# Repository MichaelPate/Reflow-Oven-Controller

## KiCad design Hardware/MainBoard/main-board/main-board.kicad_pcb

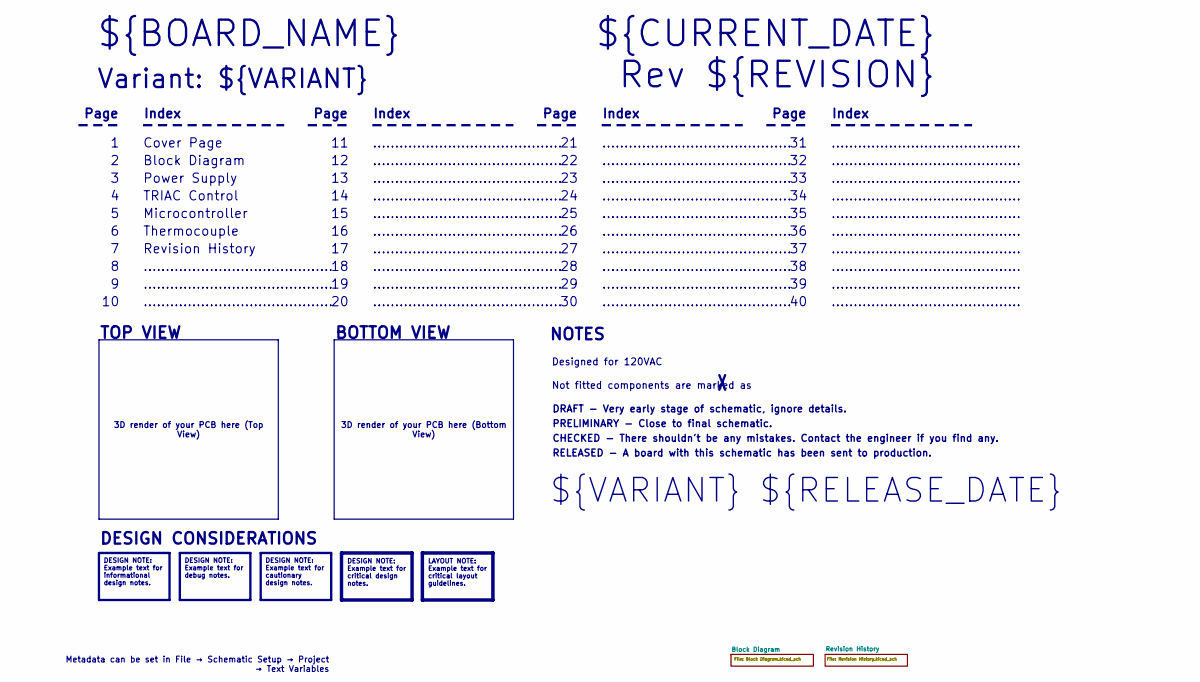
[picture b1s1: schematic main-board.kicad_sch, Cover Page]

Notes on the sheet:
BOTTOM VIEW
...........................................
RELEASED - A board with this schematic has been sent to production.
Page
TOP VIEW
Not fitted components are marked as
Index
PRELIMINARY - Close to final schematic.
${VARIANT} ${RELEASE_DATE}
TRIAC Control
${CURRENT_DATE}
Variant: ${VARIANT}
Rev ${REVISION}
Microcontroller
${BOARD_NAME}
DRAFT - Very early stage of schematic, ignore details.
Thermocouple
Block Diagram
Designed for 120VAC
Cover Page
NOTES
Power Supply
CHECKED - There shouldn't be any mistakes. Contact the engineer if you find any.
DESIGN CONSIDERATIONS
Revision History
3D render of your PCB here (Bottom View)
3D render of your PCB here (Top View)
Metadata can be set in File → Schematic Setup → Project → Text Variables
DESIGN NOTE: Example text for informational design notes.
LAYOUT NOTE: Example text for critical layout guidelines.
DESIGN NOTE: Example text for cautionary design notes.
DESIGN NOTE: Example text for debug notes.
DESIGN NOTE: Example text for critical design notes.

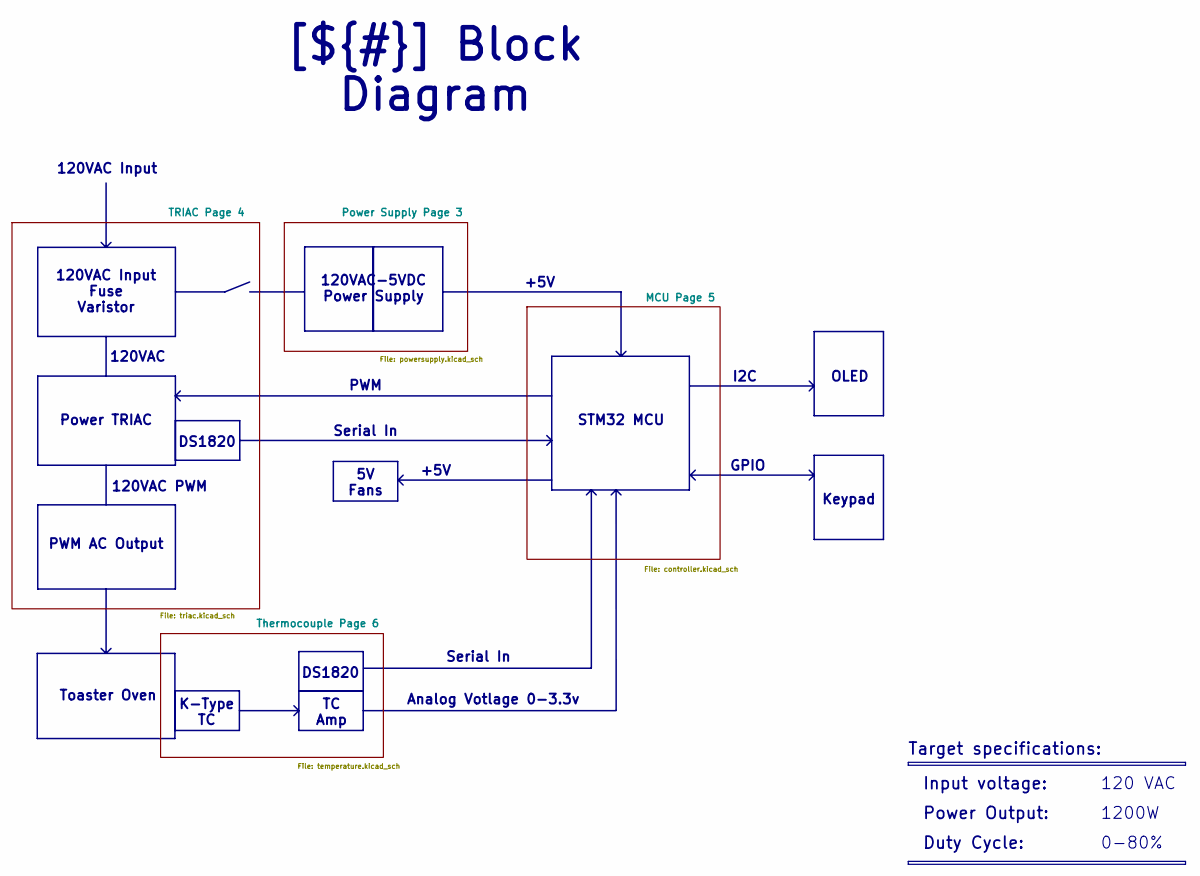
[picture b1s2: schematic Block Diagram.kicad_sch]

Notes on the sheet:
TC Amp
DS1820
PWM AC Output
+5V
GPIO
Toaster Oven
STM32 MCU
PWM
K-Type TC
120VAC
Analog Votlage 0-3.3v
5V Fans
120VAC Input
OLED
Power TRIAC
Serial In
120VAC-5VDC Power Supply
120VAC Input Fuse Varistor
120VAC PWM
Keypad
I2C
Duty Cycle:
Power Output:
Input voltage:
1200W
[${#}] ${TITLE}
Target specifications:
0-80%
120 VAC

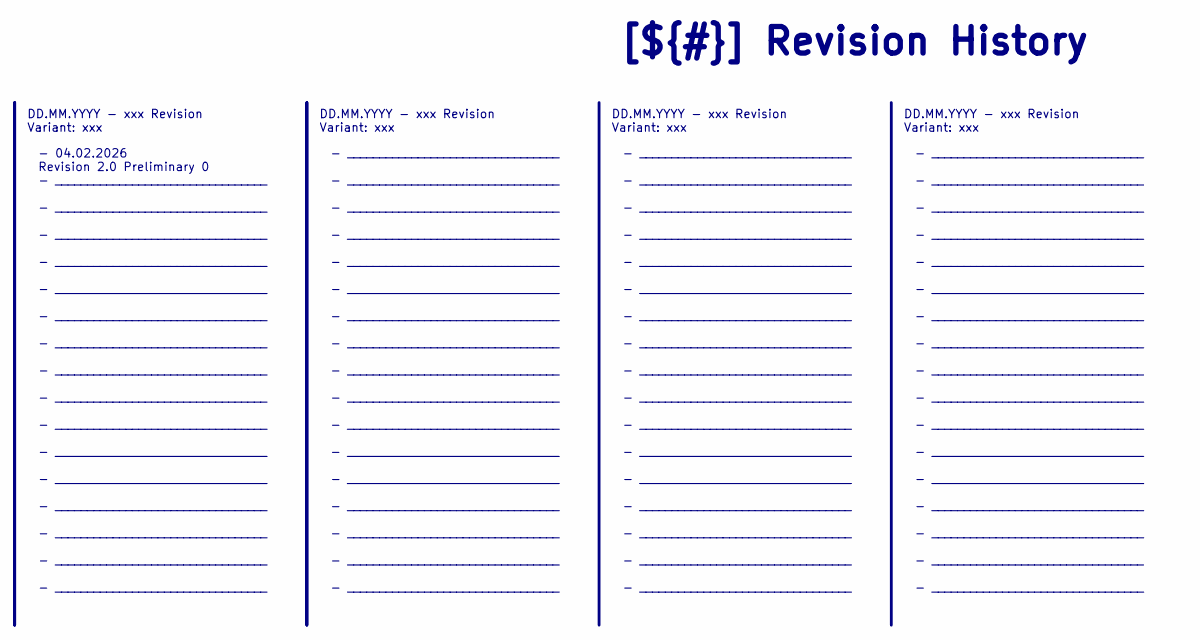
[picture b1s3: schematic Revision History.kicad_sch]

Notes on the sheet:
DD.MM.YYYY - xxx Revision Variant: xxx
[${#}] ${TITLE}
- _________________________________ - _________________________________ - _________________________________ - _________________________________ - _________________________________ - _________________________________ - _________________________________ - _________________________________ - _________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
- 04.02.2026 Revision 2.0 Preliminary 0 - _________________________________ - _________________________________ - _________________________________ - _________________________________ - _________________________________ - _________________________________ - _________________________________ - _____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

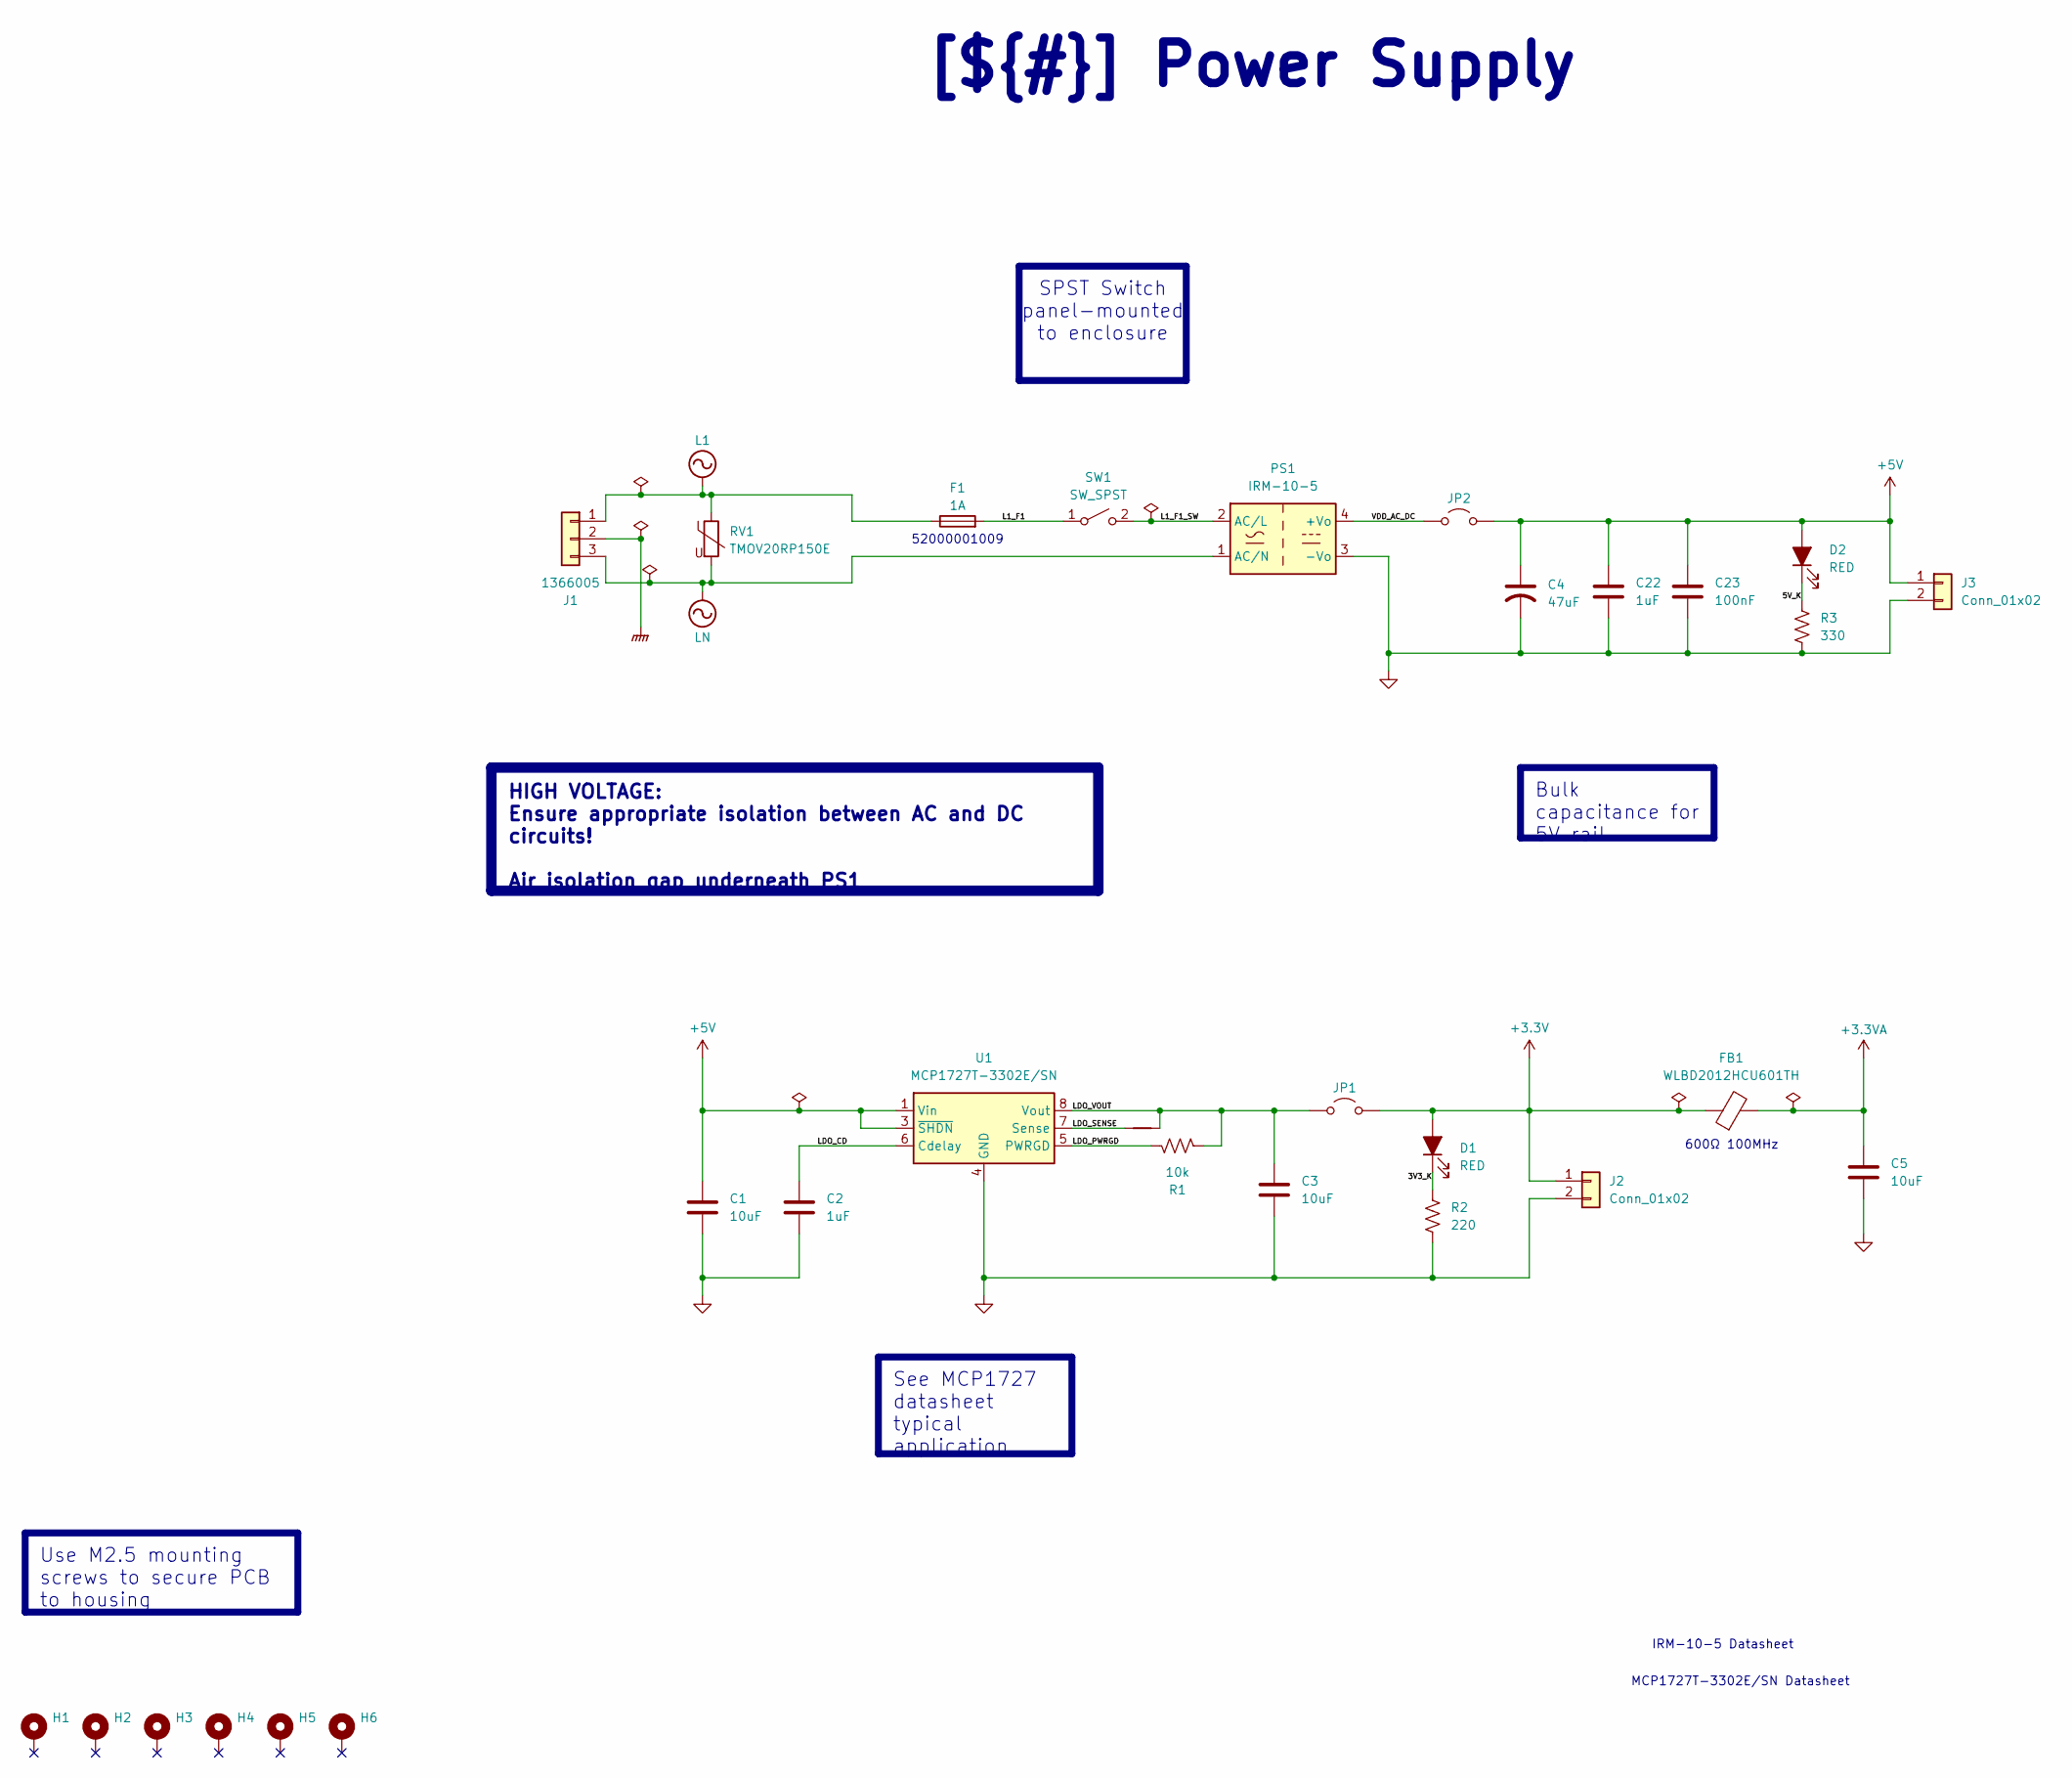
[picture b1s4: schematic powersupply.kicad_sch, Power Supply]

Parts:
C1, C3, C5: 10uF; C_0805_2012Metric_Pad1.18x1.45mm_HandSolder
C2, C22: 1uF; C_0805_2012Metric_Pad1.18x1.45mm_HandSolder
C4: 47uF; C_Radial_D5.0mm_H5.0mm_P2.00mm
C23: 100nF; C_0603_1608Metric_Pad1.08x0.95mm_HandSolder
D1, D2: RED; LED_0603_1608Metric_Pad1.05x0.95mm_HandSolder
F1: 1A; Fuseholder_Clip-5x20mm_Littelfuse_100_Inline_P20.50x4.60mm_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
FB1: WLBD2012HCU601TH; L_0805_2012Metric_Pad1.05x1.20mm_HandSolder
H1, H2, H3, H4, H5, H6: MountingHole_Pad; MountingHole_2.7mm
J1: 1366005; SPTA-THR 2.53-5.0 P26
J2, J3: Conn_01x02; TerminalBlock_Phoenix_MKDS-1,5-2-5.08_1x02_P5.08mm_Horizont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
JP1, JP2: Jumper_2_Open; PinHeader_1x02_P2.54mm_Vertical
NT2: NetTie_2; NetTie-2_SMD_Pad0.5mm
PS1: IRM-10-5; Converter_ACDC_MeanWell_IRM-10-xx_THT
R1: 10k; R_0603_1608Metric_Pad0.98x0.95mm_HandSolder
R2: 220; R_0603_1608Metric_Pad0.98x0.95mm_HandSolder
R3: 330; R_0603_1608Metric_Pad0.98x0.95mm_HandSolder
RV1: TMOV20RP150E
SW1: SW_SPST; TerminalBlock_Phoenix_MKDS-1,5-2-5.08_1x02_P5.08mm_Horizont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
U1: MCP1727T-3302E/SN; SOIC-8_3.9x4.9mm_P1.27mm

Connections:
+3.3V: D1.2 (A), FB1.1, J2.1, JP1.2 (B); also elsewhere on the board
+3.3VA: C5.1, FB1.2; also elsewhere on the board
+5V: C1.1, C4.1, C22.1, C23.1, D2.2 (A), J3.1, JP2.2 (B), U1.1 (Vin), U1.2 (Vin), U1.3 (~SHDN); also elsewhere on the board
/Block Diagram/Power Supply Page 3/3V3_K: D1.1 (K), R2.1
/Block Diagram/Power Supply Page 3/5V_K: D2.1 (K), R3.1
/Block Diagram/Power Supply Page 3/L1_F1: F1.2, SW1.1 (A)
/Block Diagram/Power Supply Page 3/L1_F1_SW: PS1.2 (AC/L), SW1.2 (B)
/Block Diagram/Power Supply Page 3/LDO_CD: C2.1, U1.6 (Cdelay)
/Block Diagram/Power Supply Page 3/LDO_PWRGD: R1.2, U1.5 (PWRGD)
/Block Diagram/Power Supply Page 3/LDO_SENSE: NT2.1, U1.7 (Sense)
/Block Diagram/Power Supply Page 3/LDO_VOUT: C3.1, JP1.1 (A), NT2.2, R1.1, U1.8 (Vout)
/Block Diagram/Power Supply Page 3/VDD_AC_DC: JP2.1 (A), PS1.4 (+Vo)
GND: C1.2, C2.2, C3.2, C4.2, C5.2, C22.2, C23.2, J2.2, J3.2, PS1.3 (-Vo), R2.2, R3.2, U1.4 (GND); also elsewhere on the board
GNDPWR: J1.2; also elsewhere on the board
L1: F1.1, J1.1, RV1.1; also elsewhere on the board
LN: J1.3, PS1.1 (AC/N), RV1.2; also elsewhere on the board

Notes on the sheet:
52000001009
600Ω 100MHz
IRM-10-5 Datasheet
MCP1727T-3302E/SN Datasheet
See MCP1727 datasheet typical application
Bulk capacitance for 5V rail
Use M2.5 mounting screws to secure PCB to housing
[${#}] ${TITLE}
SPST Switch panel-mounted to enclosure
HIGH VOLTAGE: Ensure appropriate isolation between AC and DC circuits! Air isolation gap underneath PS1

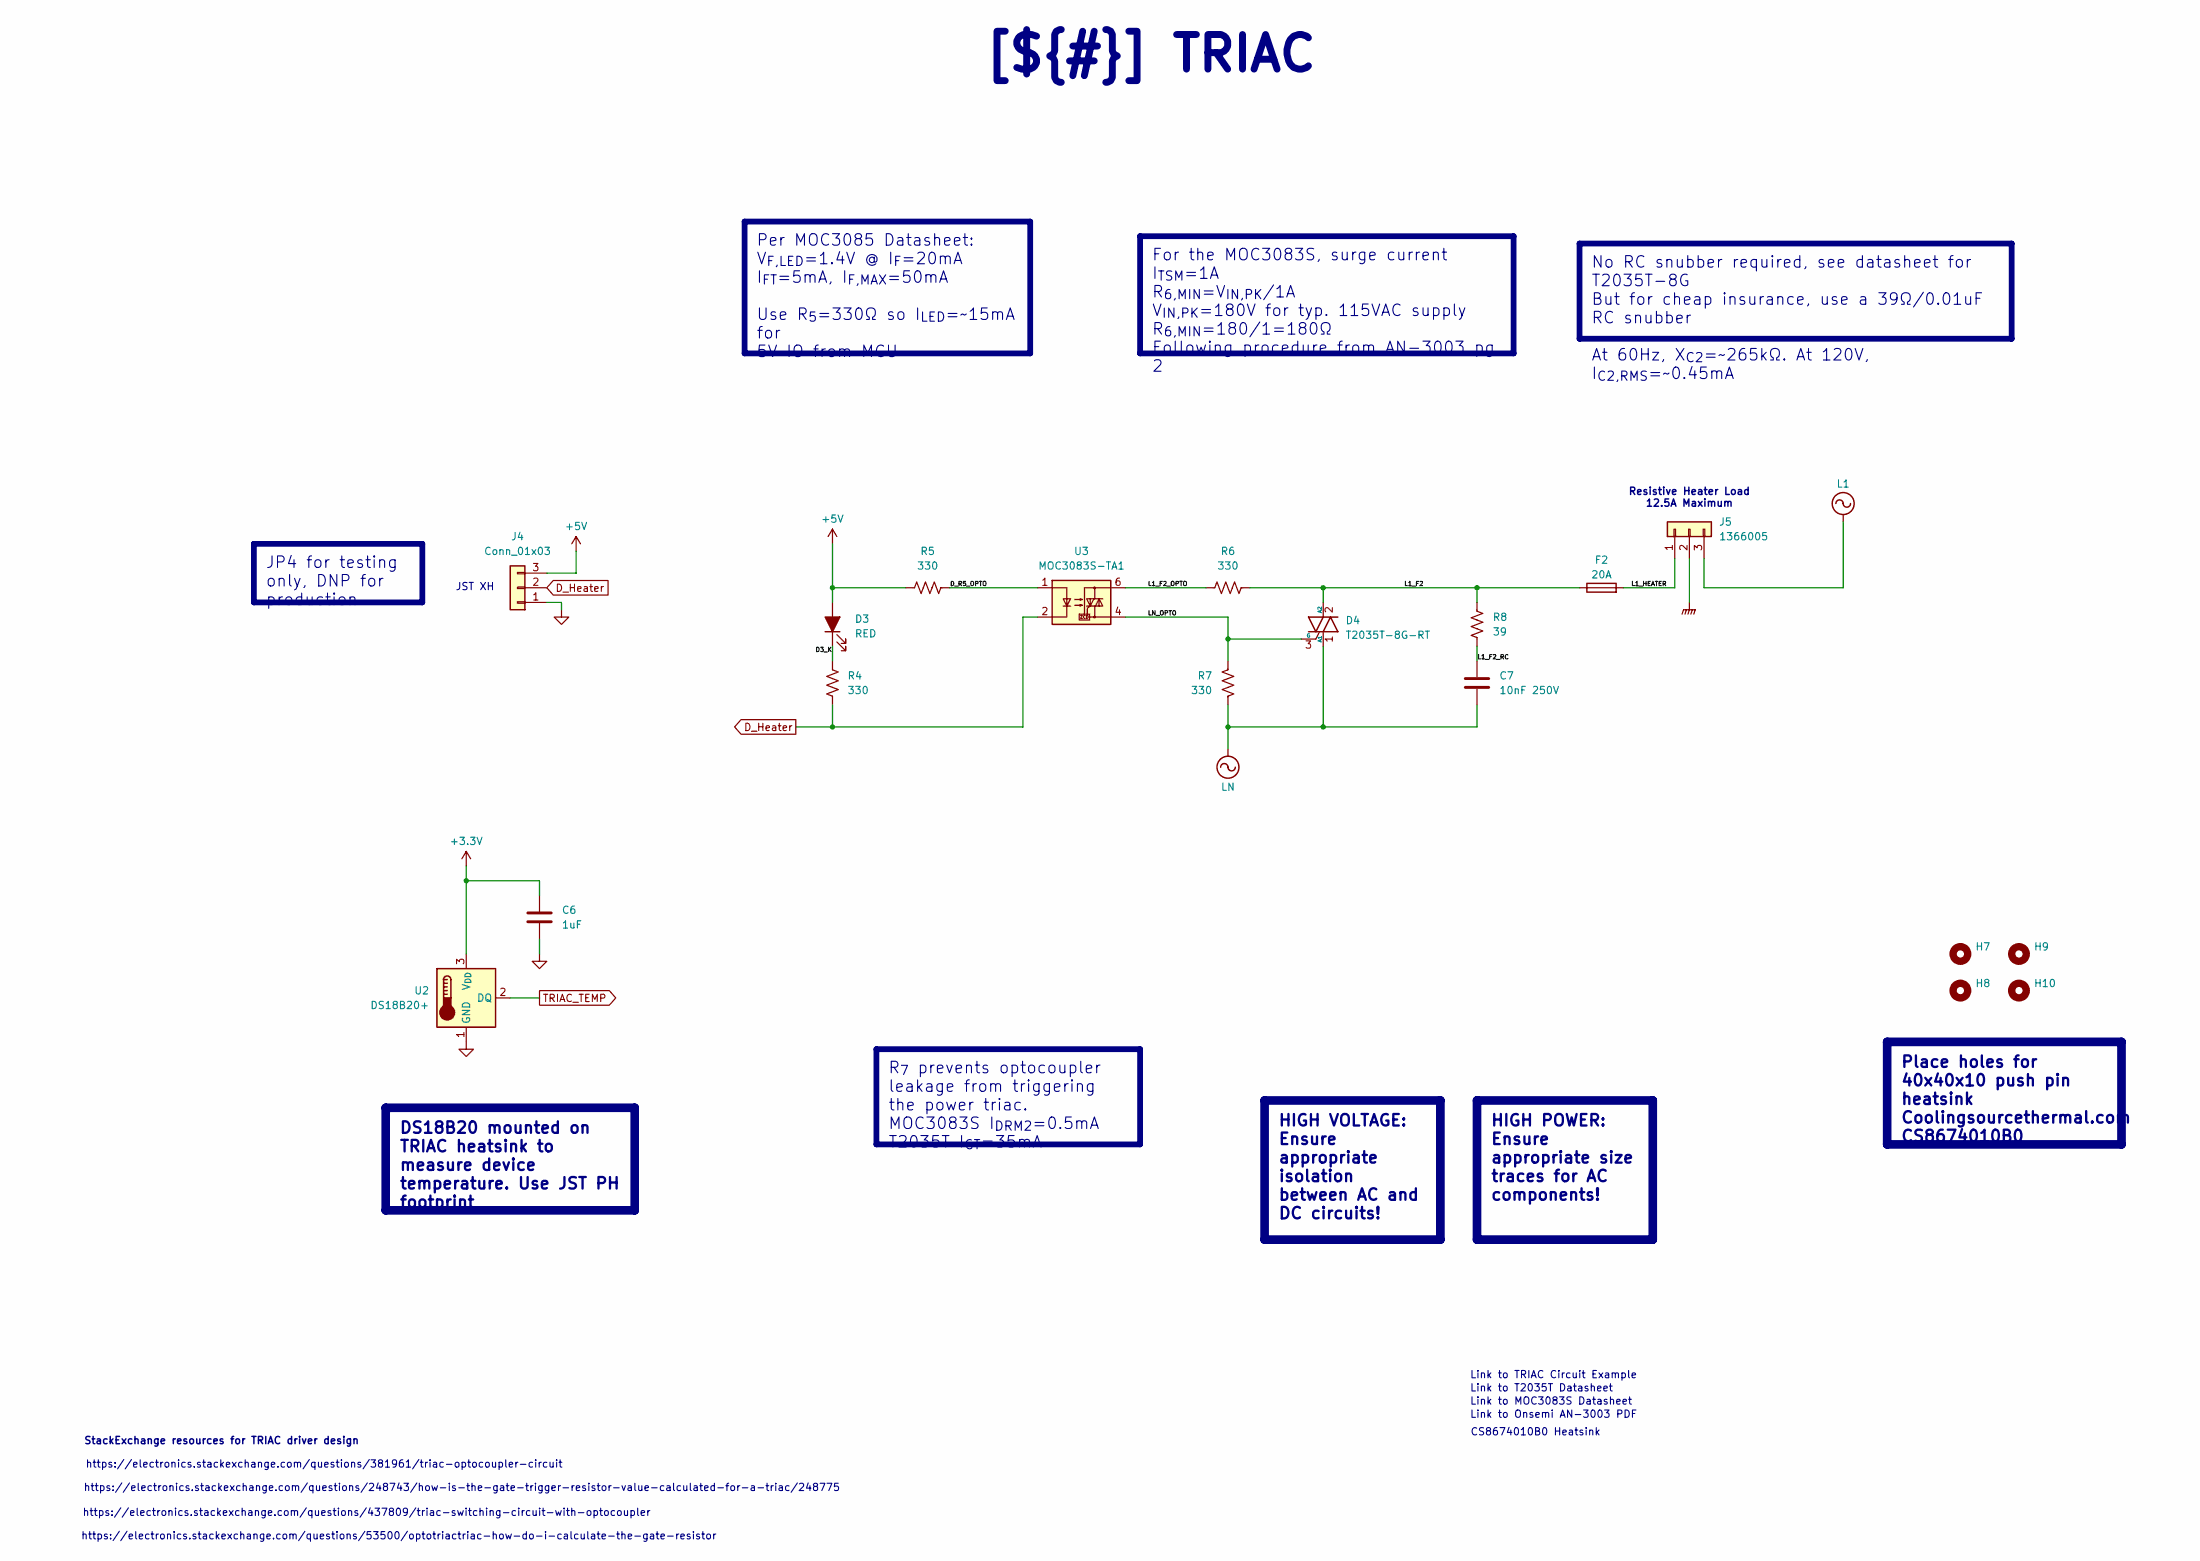
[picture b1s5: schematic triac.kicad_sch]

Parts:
C6: 1uF; C_0805_2012Metric_Pad1.18x1.45mm_HandSolder
C7: 10nF 250V; C_1812_4532Metric_Pad1.57x3.40mm_HandSolder
D3: RED; LED_0603_1608Metric_Pad1.05x0.95mm_HandSolder
D4: T2035T-8G-RT; TO-263-2
F2: 20A; Fuseholder_Clip-6.3x32mm_Littelfuse_122_Inline_P34.21x7.62m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
H7, H8, H9, H10: MountingHole; MountingHole_3mm
J4: Conn_01x03; JST_XH_B3B-XH-A_1x03_P2.50mm_Vertical
J5: 1366005; SPTA-THR 2.53-5.0 P26
R4, R5: 330; R_0603_1608Metric_Pad0.98x0.95mm_HandSolder
R6, R7: 330; R_2512_6332Metric_Pad1.40x3.35mm_HandSolder
R8: 39; R_2512_6332Metric_Pad1.40x3.35mm_HandSolder
U2: DS18B20+; JST_PH_B3B-PH-K_1x03_P2.00mm_Vertical
U3: MOC3083S-TA1; SMDIP-6_W9.53mm

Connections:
+3.3V: C6.1, U2.3 (V_{DD}); also elsewhere on the board
+5V: D3.2 (A), J4.3, R5.1; also elsewhere on the board
/Block Diagram/TRIAC Page 4/D3_K: D3.1 (K), R4.1
/Block Diagram/TRIAC Page 4/D_R5_OPTO: R5.2, U3.1
/Block Diagram/TRIAC Page 4/L1_F2: D4.2 (A2), F2.1, R6.2, R8.2
/Block Diagram/TRIAC Page 4/L1_F2_OPTO: R6.1, U3.6
/Block Diagram/TRIAC Page 4/L1_F2_RC: C7.1, R8.1
/Block Diagram/TRIAC Page 4/L1_HEATER: F2.2, J5.1
/Block Diagram/TRIAC Page 4/LN_OPTO: D4.3 (G), R7.2, U3.4
D_Heater: J4.2, R4.2, U3.2; also elsewhere on the board
GND: C6.2, J4.1, U2.1 (GND); also elsewhere on the board
GNDPWR: J5.2; also elsewhere on the board
L1: J5.3; also elsewhere on the board
LN: C7.2, D4.1 (A1), R7.1; also elsewhere on the board
TRIAC_TEMP: U2.2 (DQ); also elsewhere on the board

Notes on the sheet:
JST XH
Link to Onsemi AN-3003 PDF
https://electronics.stackexchange.com/questions/381961/triac-optocoupler-circuit
https://electronics.stackexchange.com/questions/53500/optotriactriac-how-do-i-calculate-the-gate-resistor
StackExchange resources for TRIAC driver design
Link to TRIAC Circuit Example
https://electronics.stackexchange.com/questions/437809/triac-switching-circuit-with-optocoupler
Link to MOC3083S Datasheet
https://electronics.stackexchange.com/questions/248743/how-is-the-gate-trigger-resistor-value-calculated-for-a-triac/248775
Resistive Heater Load 12.5A Maximum
CS8674010B0 Heatsink
Link to T2035T Datasheet
No RC snubber required, see datasheet for T2035T-8G But for cheap insurance, use a 39Ω/0.01uF RC snubber At 60Hz, X_{C2}=~265kΩ. At 120V, I_{C2,RMS}=~0.45mA
Place holes for 40x40x10 push pin heatsink Coolingsourcethermal.com CS8674010B0
HIGH VOLTAGE: Ensure appropriate isolation between AC and DC circuits!
HIGH POWER: Ensure appropriate size traces for AC components!
[${#}] ${TITLE}
JP4 for testing only, DNP for production
DS18B20 mounted on TRIAC heatsink to measure device temperature. Use JST PH footprint
R_{7} prevents optocoupler leakage from triggering the power triac. MOC3083S I_{DRM2}=0.5mA T2035T I_{GT}=35mA
For the MOC3083S, surge current I_{TSM}=1A R_{6,MIN}=V_{IN,PK}/1A V_{IN,PK}=180V for typ. 115VAC supply R_{6,MIN}=180/1=180Ω Following procedure from AN-3003 pg. 2
Per MOC3085 Datasheet: V_{F,LED}=1.4V @ I_{F}=20mA I_{FT}=5mA, I_{F,MAX}=50mA Use R_{5}=330Ω so I_{LED}=~15mA for 5V IO from MCU

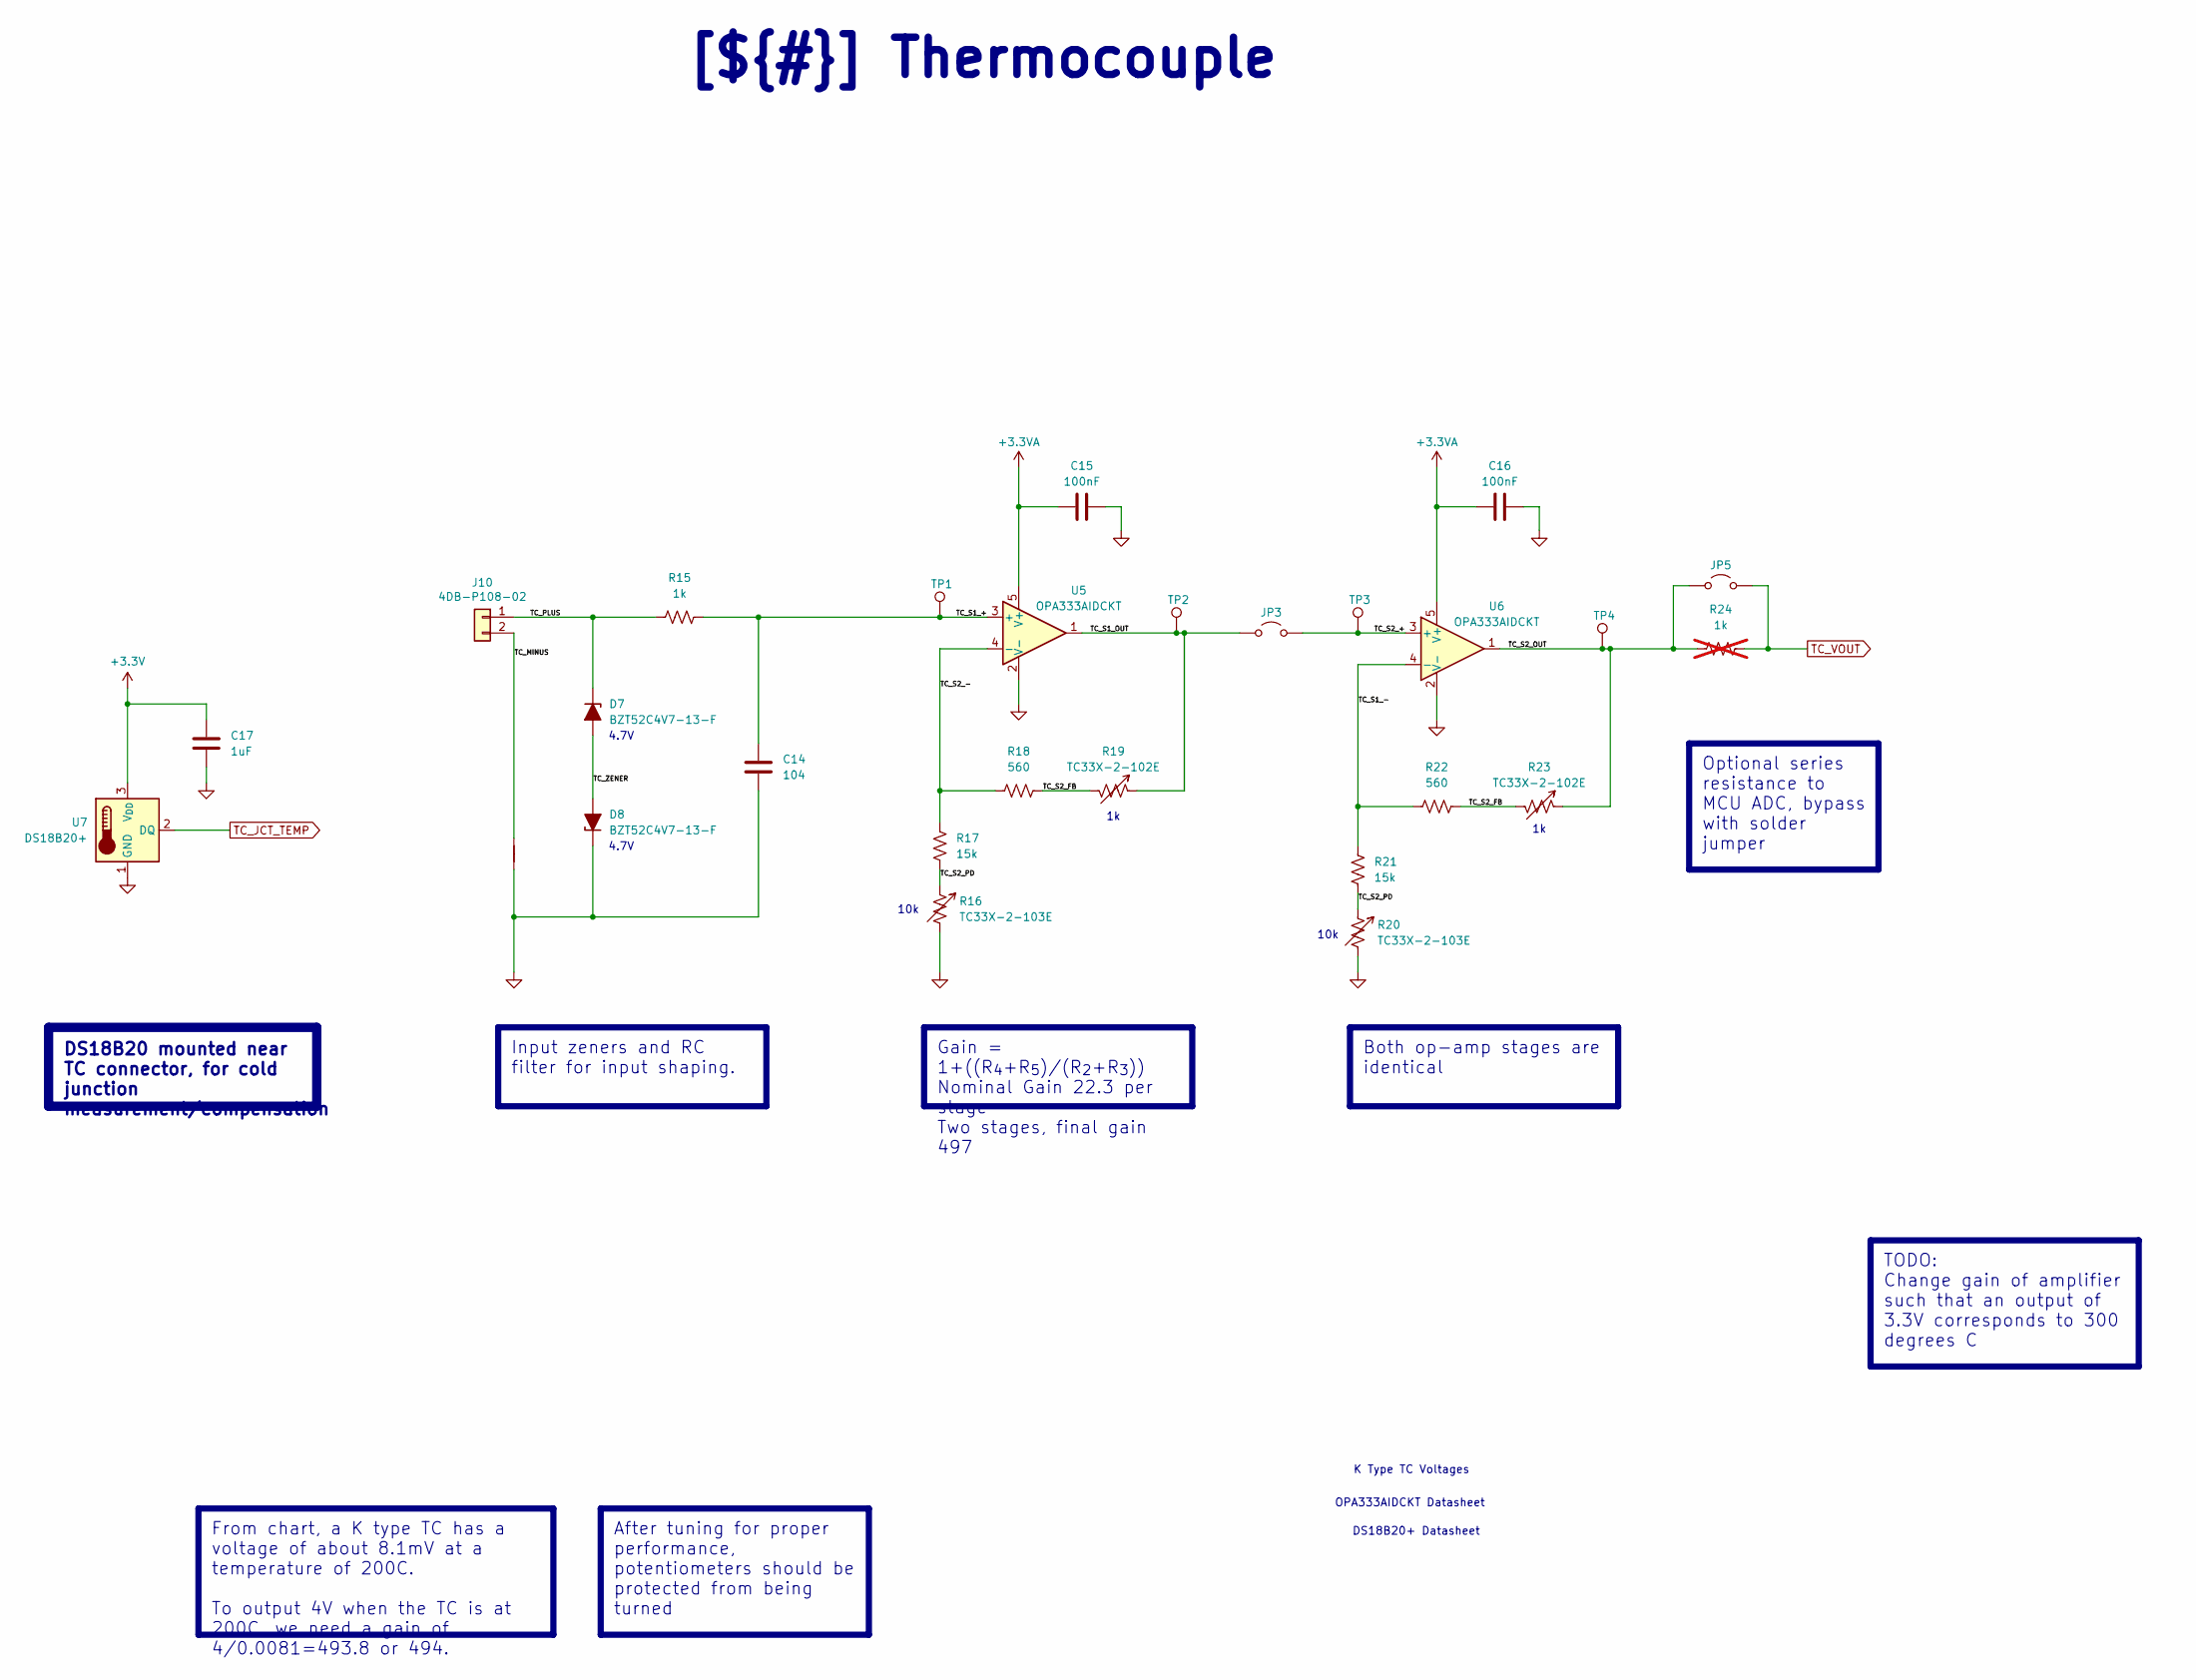
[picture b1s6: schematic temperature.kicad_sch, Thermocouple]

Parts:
C14: 104; C_0603_1608Metric_Pad1.08x0.95mm_HandSolder
C15, C16: 100nF; C_0805_2012Metric_Pad1.18x1.45mm_HandSolder
C17: 1uF; C_0805_2012Metric_Pad1.18x1.45mm_HandSolder
D7, D8: BZT52C4V7-13-F; D_SOD-123
J10: 4DB-P108-02; CONN_4DB-P108-02_TEC
JP3: Jumper_2_Open; PinHeader_1x02_P2.54mm_Vertical
JP5: Jumper_2_Open; SolderJumper-2_P1.3mm_Open_TrianglePad1.0x1.5mm
NT1: NetTie_2; NetTie-2_SMD_Pad0.5mm
R15: 1k; R_0603_1608Metric_Pad0.98x0.95mm_HandSolder
R16, R20: TC33X-2-103E; Potentiometer_Bourns_TC33X_Vertical
R17, R21: 15k; R_0603_1608Metric_Pad0.98x0.95mm_HandSolder
R18, R22: 560; R_0603_1608Metric_Pad0.98x0.95mm_HandSolder
R19, R23: TC33X-2-102E; Potentiometer_Bourns_TC33X_Vertical
R24: 1k; R_0603_1608Metric_Pad0.98x0.95mm_HandSolder; not fitted
TP1, TP2, TP3, TP4: TestPoint; PinHeader_1x01_P2.54mm_Vertical
U5, U6: OPA333AIDCKT; SOIC-8_3.9x4.9mm_P1.27mm
U7: DS18B20+; TO-92_Inline

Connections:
+3.3V: C17.1, U7.3 (V_{DD}); also elsewhere on the board
+3.3VA: C15.1, C16.1, U5.5 (V+), U6.5 (V+); also elsewhere on the board
/Block Diagram/Thermocouple Page 6/TC_MINUS: J10.2, NT1.2
/Block Diagram/Thermocouple Page 6/TC_PLUS: D7.1 (K), J10.1, R15.1
/Block Diagram/Thermocouple Page 6/TC_S1_+: C14.1, R15.2, TP1.1, U5.3 (+)
/Block Diagram/Thermocouple Page 6/TC_S1_-: R21.1, R22.1, U6.4 (-)
/Block Diagram/Thermocouple Page 6/TC_S1_OUT: JP3.1 (A), R19.1, TP2.1, U5.1
/Block Diagram/Thermocouple Page 6/TC_S2_+: JP3.2 (B), TP3.1, U6.3 (+)
/Block Diagram/Thermocouple Page 6/TC_S2_-: R17.1, R18.1, U5.4 (-)
/Block Diagram/Thermocouple Page 6/TC_S2_FB: R18.2, R19.2, R22.2, R23.2
/Block Diagram/Thermocouple Page 6/TC_S2_OUT: JP5.1 (A), R23.1, R24.1, TP4.1, U6.1
/Block Diagram/Thermocouple Page 6/TC_S2_PD: R16.1, R17.2, R20.1, R21.2
/Block Diagram/Thermocouple Page 6/TC_ZENER: D7.2 (A), D8.2 (A)
GND: C14.2, C15.2, C16.2, C17.2, D8.1 (K), NT1.1, R16.2, R20.2, U5.2 (V-), U6.2 (V-), U7.1 (GND); also elsewhere on the board
TC_JCT_TEMP: U7.2 (DQ); also elsewhere on the board
TC_VOUT: JP5.2 (B), R24.2; also elsewhere on the board

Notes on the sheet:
OPA333AIDCKT Datasheet
4.7V
10k
DS18B20+ Datasheet
K Type TC Voltages
From chart, a K type TC has a voltage of about 8.1mV at a temperature of 200C. To output 4V when the TC is at 200C, we need a gain of 4/0.0081=493.8 or 494.
DS18B20 mounted near TC connector, for cold junction measurement/compensation
After tuning for proper performance, potentiometers should be protected from being turned
Input zeners and RC filter for input shaping.
Optional series resistance to MCU ADC, bypass with solder jumper
Gain = 1+((R_{4}+R_{5})/(R_{2}+R_{3})) Nominal Gain 22.3 per stage Two stages, final gain 497
TODO: Change gain of amplifier such that an output of 3.3V corresponds to 300 degrees C
[${#}] ${TITLE}
Both op-amp stages are identical
